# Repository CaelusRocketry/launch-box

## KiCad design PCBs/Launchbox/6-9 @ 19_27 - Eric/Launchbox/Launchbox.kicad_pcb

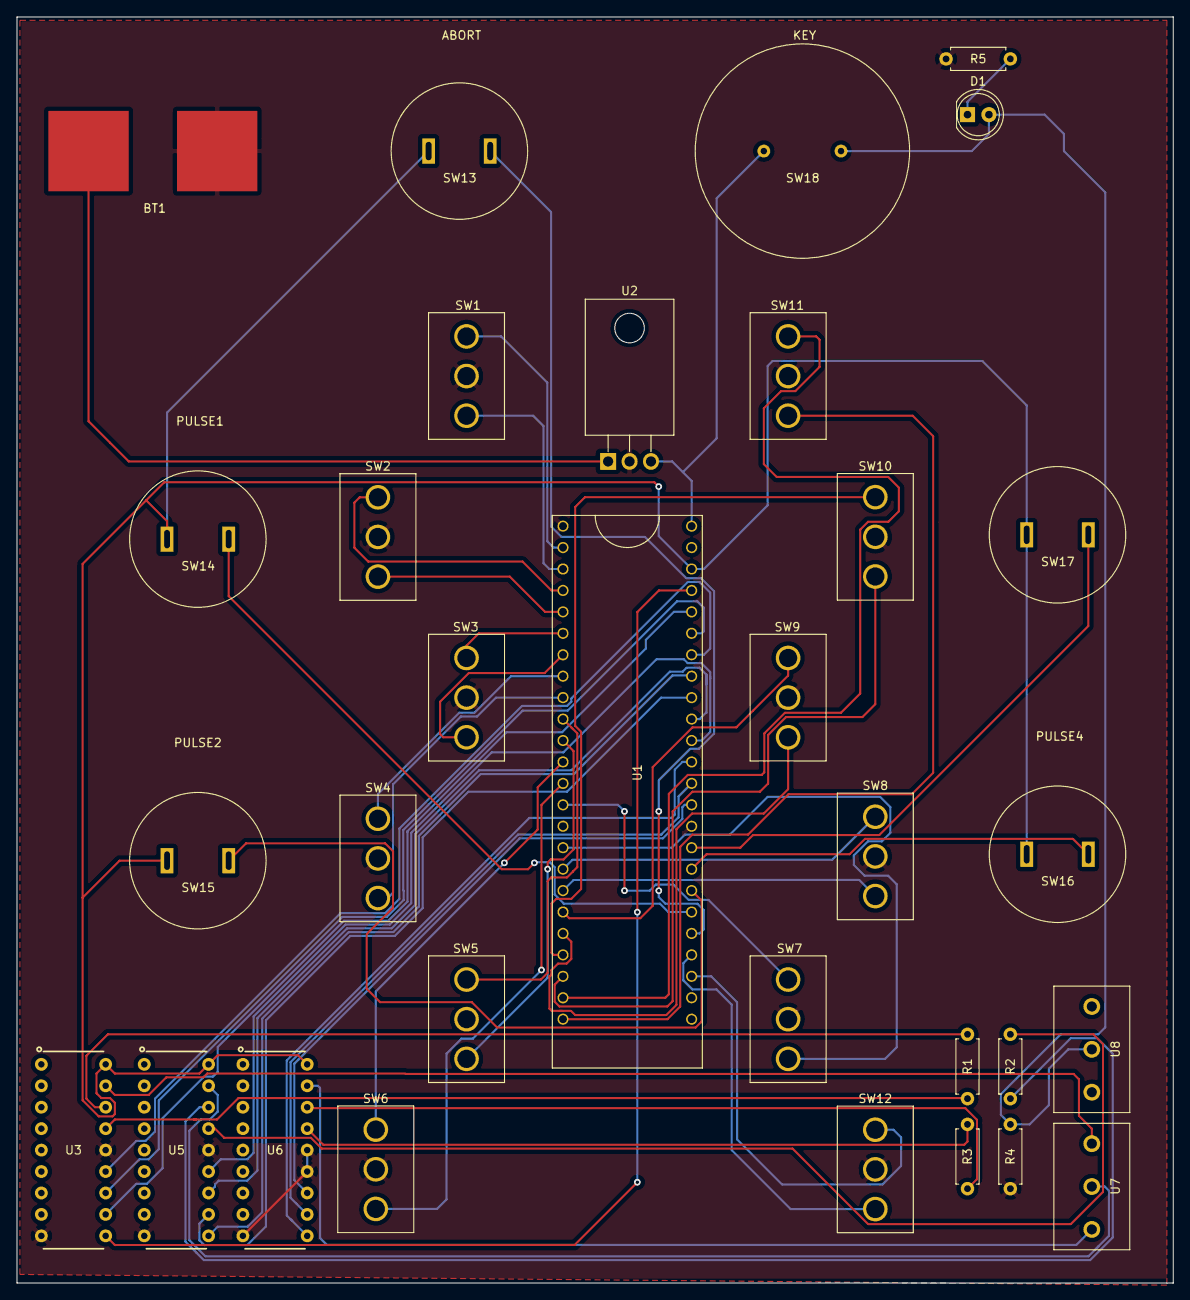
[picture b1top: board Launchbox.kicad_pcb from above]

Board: 2 copper layers, 137.0 x 150.0 mm, 32 parts (0 on the bottom side), 55 nets.

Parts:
BT1: Battery_Cell; Lipo_Battery_Connector
D1: LED; LED_D5.0mm
R1, R2, R3, R4, R5: R_US; R_Axial_DIN0207_L6.3mm_D2.5mm_P7.62mm_Horizontal
SW1, SW2, SW3, SW4, SW5, SW6, SW7, SW8, SW9, SW10, SW11, SW12: SW_SPDT_MSM; SPDT_Slide_Switch
SW13, SW14, SW15, SW16, SW17, SW18: SW_Push; Pushbutton
U1: Teensy3.6; Teensy 3.6
U2: L7805; TO-220F-3_Horizontal_TabDown
U3, U5, U6: HT12E
U7, U8: SerialScrewTerminals; ScrewTerminals

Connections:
3.3V: SW13.1, SW14.1, SW15.1, SW16.1, SW17.1, U1.42, U3.18, U5.18, U6.18
GND: BT1.2, R4.1, R5.1, SW1.2, SW2.2, SW3.2, SW4.2, SW5.2, SW6.2, SW7.2, SW8.2, SW9.2, SW10.2, SW11.2, SW12.2, U1.43, U1.46, U2.2, U3.9, U3.14, U5.9, U5.14, U6.9, U6.13, U6.14, U8.1
unnamed: D1.1, R5.2
unnamed: D1.2, R4.2, SW18.2, U8.2
unnamed: R1.1, U3.16
unnamed: R1.2, U3.15
unnamed: R2.1, U5.16
unnamed: R2.2, U5.15
unnamed: R3.1, U6.16
unnamed: R3.2, U6.15
unnamed: SW1.1, U1.0
unnamed: SW1.3, U1.1
unnamed: SW2.1, U1.2
unnamed: SW2.3, U1.3
unnamed: SW3.1, U1.4
unnamed: SW3.3, U1.5
unnamed: SW4.1, U1.6
unnamed: SW4.3, U1.7
unnamed: SW5.1, U1.8
unnamed: SW5.3, U1.9
unnamed: SW6.1, U1.10
unnamed: SW6.3, U1.11
unnamed: SW7.1, U1.12
unnamed: SW7.3, U1.24
unnamed: SW8.1, U1.25
unnamed: SW8.3, U1.26
unnamed: SW9.1, U1.27
unnamed: SW9.3, U1.28
unnamed: SW10.1, U1.29
unnamed: SW10.3, U1.30
unnamed: SW11.1, U1.31
unnamed: SW11.3, U1.32
unnamed: SW12.1, U1.35
unnamed: SW12.3, U1.36
unnamed: SW13.2, U1.37
unnamed: SW14.2, U1.38
unnamed: SW15.2, U1.39
unnamed: SW16.2, U1.45
unnamed: SW17.2, U1.44
unnamed: SW18.1, U1.40, U2.3
unnamed: U1.13, U6.12
unnamed: U1.14, U6.11
unnamed: U1.15, U6.10
unnamed: U1.16, U5.13
unnamed: U1.17, U5.12
unnamed: U1.18, U5.11
unnamed: U1.19, U5.10
unnamed: U1.20, U3.13
unnamed: U1.21, U3.12
unnamed: U1.22, U3.11
unnamed: U1.23, U3.10
unnamed: U3.17, U7.3
unnamed: U5.17, U7.2
unnamed: U6.17, U7.1
VCC: BT1.1, U2.1

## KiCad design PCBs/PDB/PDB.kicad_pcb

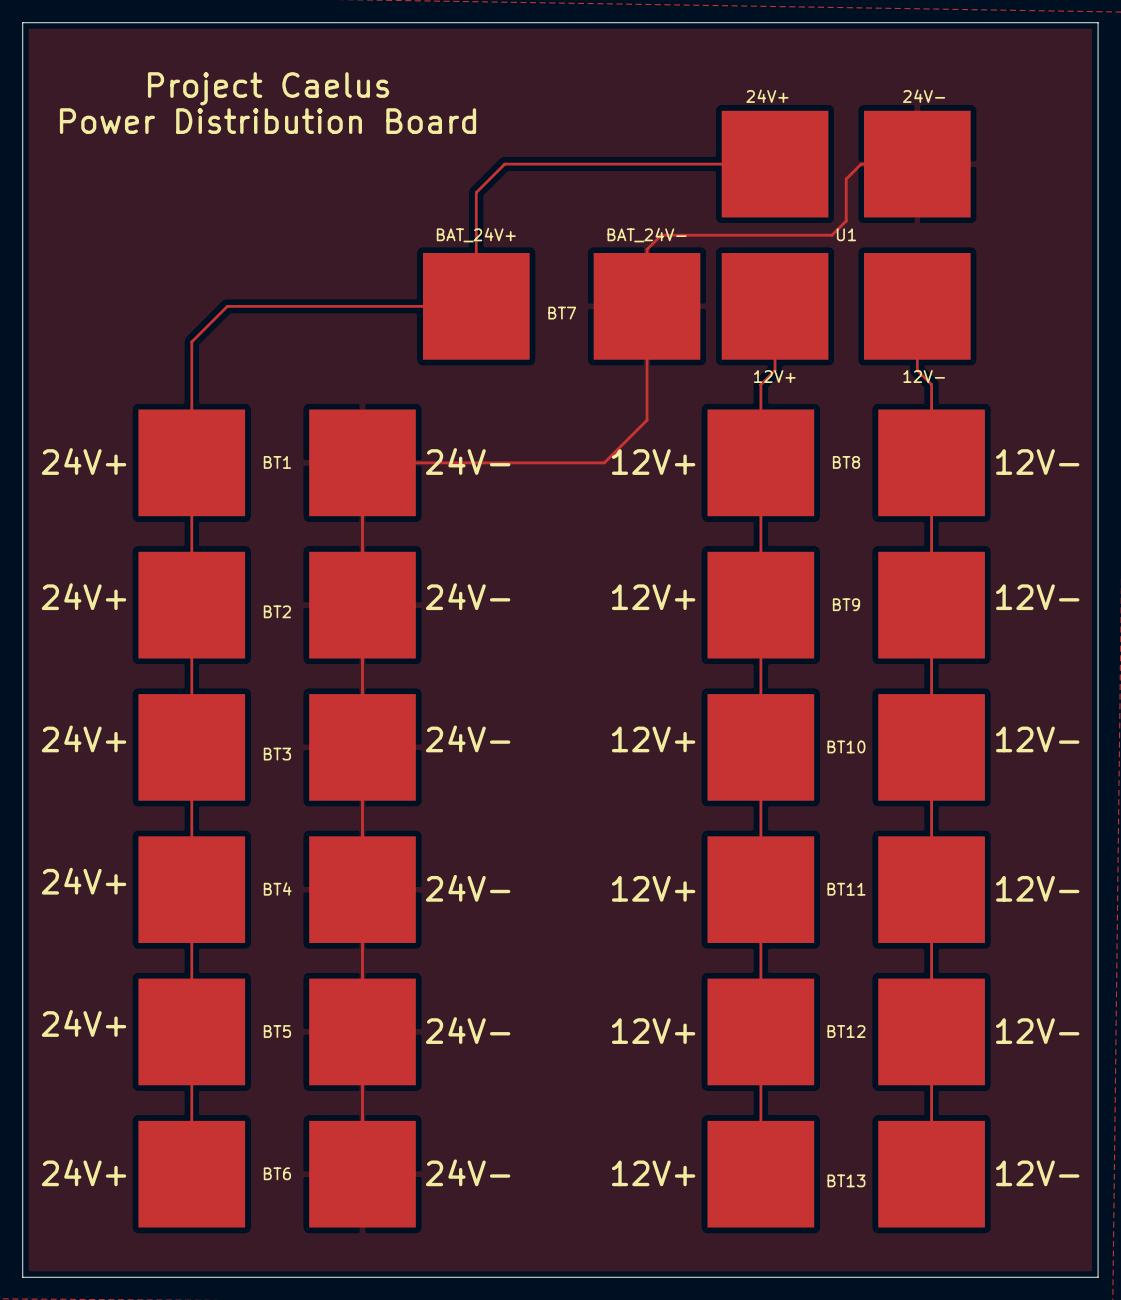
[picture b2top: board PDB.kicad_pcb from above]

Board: 2 copper layers, 96.0 x 112.0 mm, 14 parts (0 on the bottom side), 4 nets.

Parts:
BT1, BT2, BT3, BT4, BT5, BT6, BT7, BT8, BT9, BT10, BT11, BT12, BT13: Battery_Cell; Lipo_Battery_Connector
U1: 24V_12V_Regulator

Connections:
unnamed: BT1.1, BT2.1, BT3.1, BT4.1, BT5.1, BT6.1, BT7.1, U1.1
unnamed: BT1.2, BT2.2, BT3.2, BT4.2, BT5.2, BT6.2, BT7.2, U1.2
unnamed: BT8.1, BT9.1, BT10.1, BT11.1, BT12.1, BT13.1, U1.3
unnamed: BT8.2, BT9.2, BT10.2, BT11.2, BT12.2, BT13.2, U1.4

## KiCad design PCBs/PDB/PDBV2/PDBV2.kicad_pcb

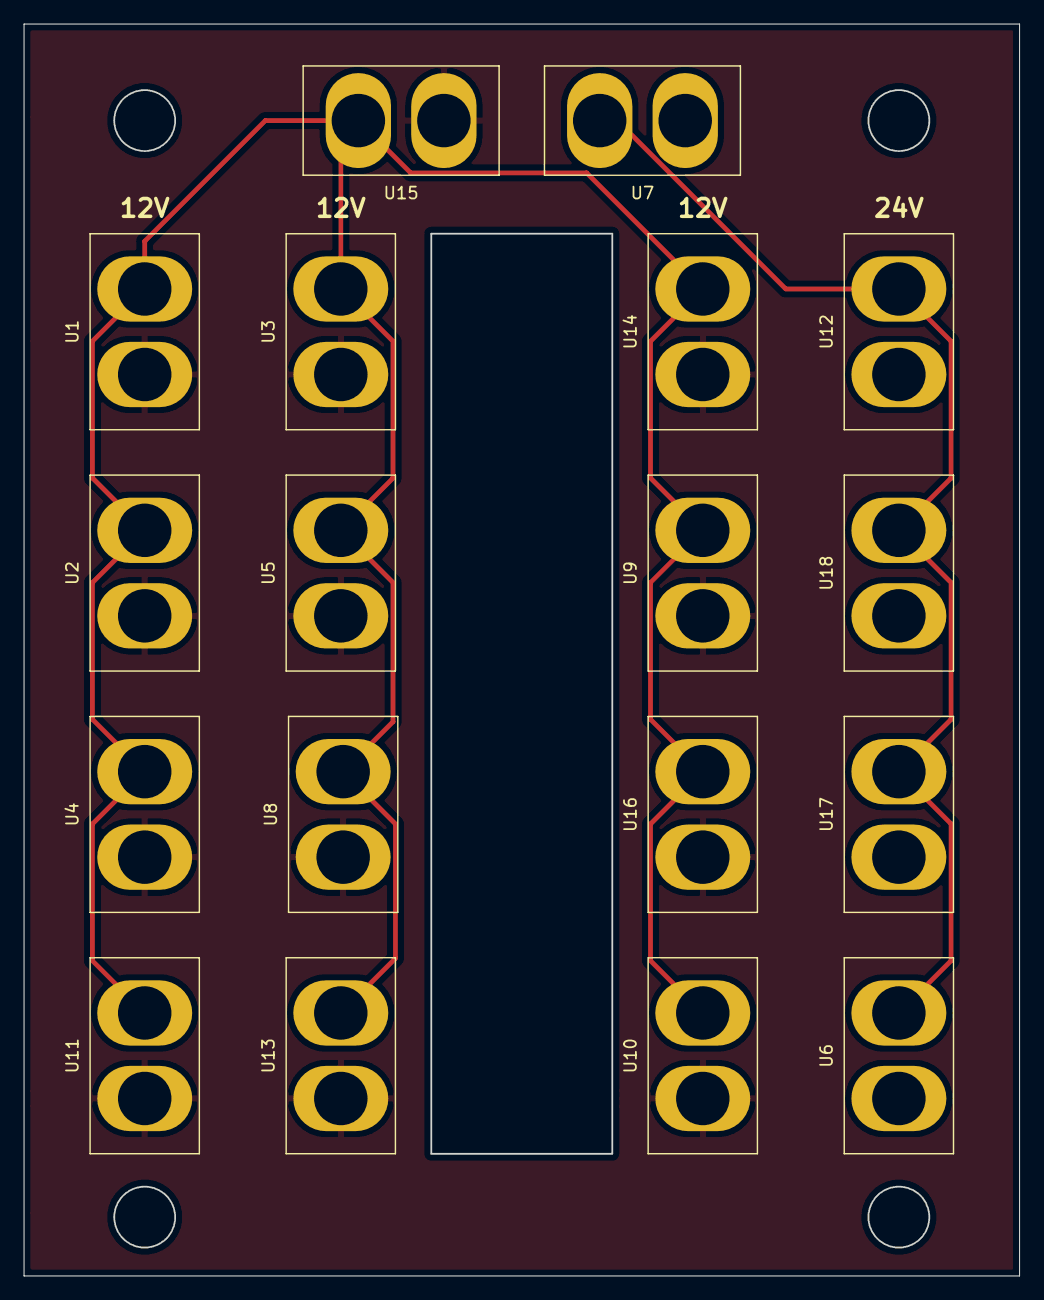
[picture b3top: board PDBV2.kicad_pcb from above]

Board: 2 copper layers, 83.8 x 105.4 mm, 18 parts (0 on the bottom side), 4 nets.

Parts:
U1, U2, U3, U4, U5, U8, U9, U10, U11, U13, U14, U15, U16: XT60H-M12; XT60H-MTH
U6, U7, U12, U17, U18: XT60H-M24; XT60H-MTH

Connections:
GND: U1.2, U2.2, U3.2, U4.2, U5.2, U8.2, U9.2, U10.2, U11.2, U13.2, U14.2, U15.2, U16.2
GND24: U6.2, U7.2, U12.2, U17.2, U18.2
unnamed: U1.1, U2.1, U3.1, U4.1, U5.1, U8.1, U9.1, U10.1, U11.1, U13.1, U14.1, U15.1, U16.1
unnamed: U6.1, U7.1, U12.1, U17.1, U18.1

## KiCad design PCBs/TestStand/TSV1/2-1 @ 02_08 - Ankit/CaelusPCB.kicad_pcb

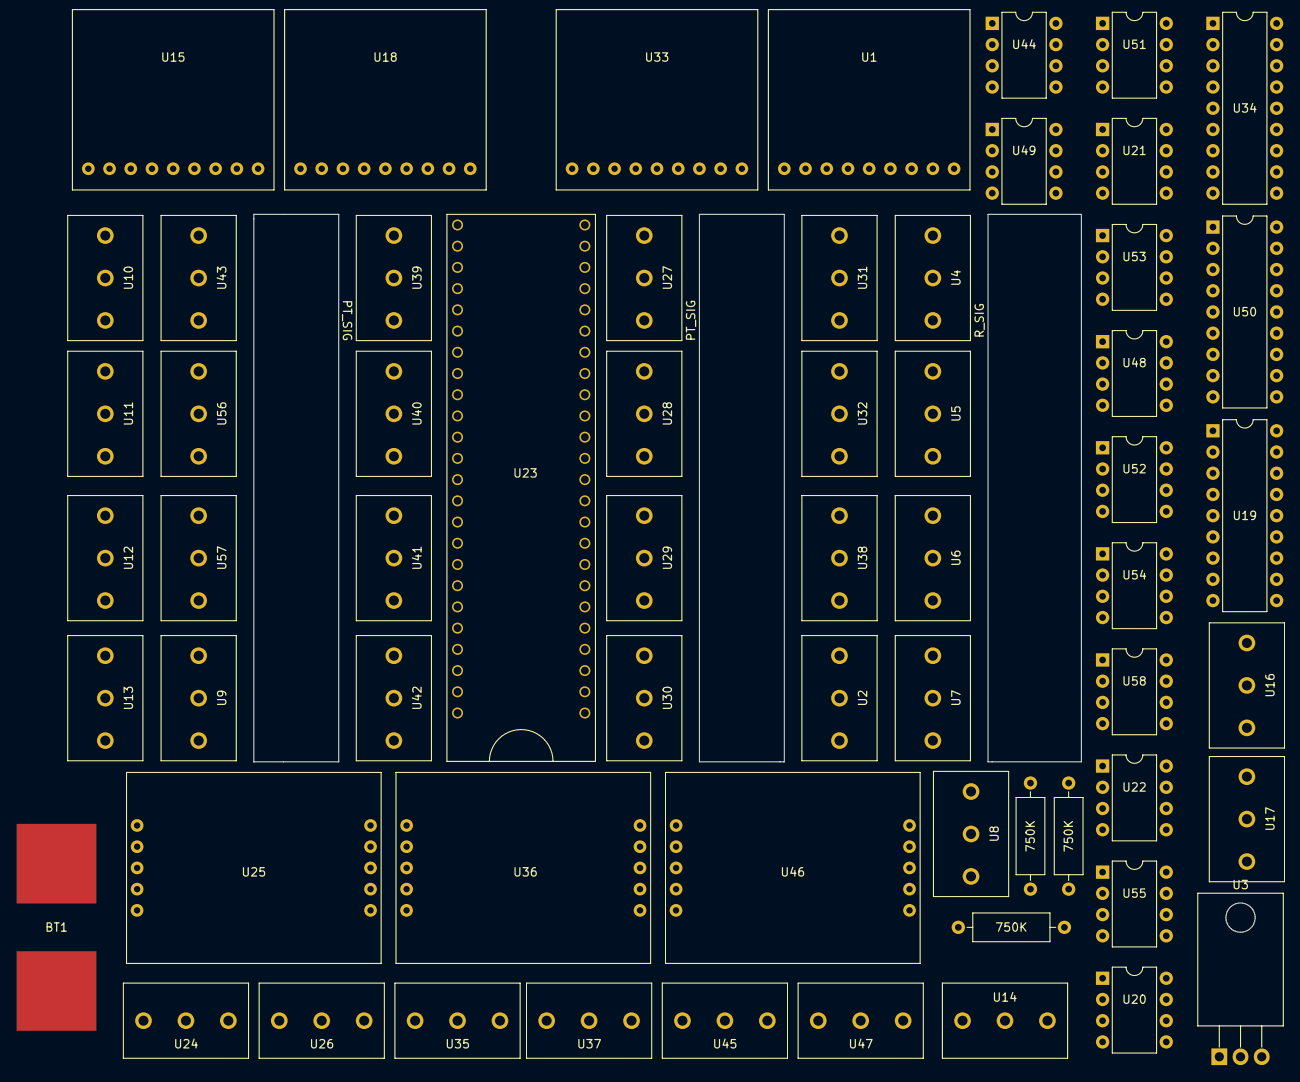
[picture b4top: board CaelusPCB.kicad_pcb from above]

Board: 2 copper layers, 62 parts (0 on the bottom side), 91 nets, no tracks yet.

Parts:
750K, 750K#2, 750K#3: R_US; R_Axial_DIN0309_L9.0mm_D3.2mm_P12.70mm_Horizontal
BT1: Battery_Cell; Lipo_Battery_Connector
U1, U15, U18, U33: MAX31856
U2, U4, U5, U6, U7, U8, U9, U10, U11, U12, U13, U14, U16, U17, U24, U26, U27, U28, U29, U30, U31, U32, U35, U37, U38, U39, U40, U41, U42, U43, U45, U47, U56, U57: SerialScrewTerminals; ScrewTerminals
U3: L7805; TO-220-3_Horizontal_TabDown
U19, U34, U50: Launchbox_HT12D; DIP-18_W7.62mm
U20, U21, U22, U44, U48, U49, U51, U52, U53, U54, U55, U58: SPDT_IC; DIP-8_W7.62mm
U23: Teensy3.6; Teensy 3.6
U25, U36, U46: LoadCellAmp

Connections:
1: U1.4, U15.4, U18.4, U23.32, U33.4
2: U23.31, U33.7
3: U20.2, U23.3
4: U23.4, U44.2
5: U23.5, U51.2
6: U21.2, U23.6
7: U23.7, U48.2
8: U23.8, U52.2
9: U23.9, U54.2
10: U23.10, U58.2
11: U22.2, U23.11
12: U23.12, U49.2
13: U1.6, U15.6, U18.6, U23.0, U33.6
14: U1.5, U15.5, U18.5, U23.1, U33.5
15: U18.7, U23.2
16: U23.25, U25.8
17: U23.26, U25.7
18: U23.27, U36.8
19: U23.28, U36.7
20: U23.29, U46.8
21: U23.30, U46.7
25: U17.1, U50.14
26: U17.2, U34.14
27: U17.3, U19.14
28: U20.8, U50.13
29: U44.8, U50.12
30: U50.11, U51.8
31: U21.8, U50.10
32: U34.13, U48.8
33: U34.12, U52.8
34: U34.11, U54.8
35: U34.10, U58.8
36: U19.13, U22.8
37: U19.12, U49.8
38: U19.11, U53.8
39: U19.10, U55.8
40: U2.1, U20.1
41: U4.1, U44.1
42: U5.1, U51.1
43: U6.1, U21.1
44: U7.1, U48.1
45: U8.1, U52.1
46: U12.1, U54.1
47: U13.1, U58.1
48: U11.1, U22.1
49: U14.1, U49.1
50: U15.7, U23.33
51: U1.7, U23.34
52: U16.1, U20.6, U21.6, U22.6, U44.6, U48.6, U49.6, U51.6, U52.6, U53.6, U54.6, U55.6, U58.6
53: U9.1, U53.1
54: U10.1, U55.1
55: U23.36, U56.1
56: U23.39, U57.1
57: U23.13, U53.2
58: U23.35, U55.2
+5V: U1.1, U2.2, U3.3, U4.2, U5.2, U6.2, U7.2, U8.2, U9.2, U10.2, U11.2, U12.2, U13.2, U14.2, U15.1, U18.1, U19.17, U19.18, U20.4, U20.5, U21.4, U21.5, U22.4, U22.5, U23.40, U25.9, U25.10, U27.2, U28.2, U29.2, U30.2, U31.2, U32.2, U33.1, U34.17, U34.18, U36.9, U36.10, U38.2, U39.2, U40.2, U41.2, U42.2, U43.2, U44.4, U44.5, U46.9, U46.10, U48.4, U48.5, U49.4, U49.5, U50.17, U50.18, U51.4, U51.5, U52.4, U52.5, U53.4, U53.5, U54.4, U54.5, U55.4, U55.5, U56.2, U57.2, U58.4, U58.5
GND1: BT1.2, U1.3, U2.3, U3.2, U4.3, U5.3, U6.3, U7.3, U8.3, U9.3, U10.3, U11.3, U12.3, U13.3, U14.3, U15.3, U16.2, U18.3, U19.1, U19.2, U19.3, U19.4, U19.5, U19.6, U19.7, U19.8, U19.9, U20.3, U20.7, U21.3, U21.7, U22.3, U22.7, U23.46, U25.6, U27.3, U28.3, U29.3, U30.3, U31.3, U32.3, U33.3, U34.1, U34.2, U34.3, U34.4, U34.5, U34.6, U34.7, U34.8, U34.9, U36.6, U38.3, U39.3, U40.3, U41.3, U42.3, U43.3, U44.3, U44.7, U46.6, U48.3, U48.7, U49.3, U49.7, U50.1, U50.2, U50.3, U50.4, U50.5, U50.6, U50.7, U50.8, U50.9, U51.3, U51.7, U52.3, U52.7, U53.3, U53.7, U54.3, U54.7, U55.3, U55.7, U56.3, U57.3, U58.3, U58.7
unnamed: BT1.1, U3.1
unnamed: 750K.1, U19.16
unnamed: 750K.2, U19.15
unnamed: 750K#2.1, U34.16
unnamed: 750K#2.2, U34.15
unnamed: 750K#3.1, U50.16
unnamed: 750K#3.2, U50.15
unnamed: U23.14, U42.1
unnamed: U23.15, U31.1
unnamed: U23.16, U41.1
unnamed: U23.17, U30.1
unnamed: U23.18, U40.1
unnamed: U23.19, U29.1
unnamed: U23.20, U39.1
unnamed: U23.21, U28.1
unnamed: U23.22, U38.1
unnamed: U23.23, U27.1
unnamed: U23.37, U43.1
unnamed: U23.38, U32.1
unnamed: U24.1, U25.4
unnamed: U24.2, U25.5
unnamed: U25.1, U26.1
unnamed: U25.2, U26.2
unnamed: U25.3, U26.3
unnamed: U35.1, U36.4
unnamed: U35.2, U36.5
unnamed: U36.1, U37.1
unnamed: U36.2, U37.2
unnamed: U36.3, U37.3
unnamed: U45.1, U46.4
unnamed: U45.2, U46.5
unnamed: U46.1, U47.1
unnamed: U46.2, U47.2
unnamed: U46.3, U47.3
